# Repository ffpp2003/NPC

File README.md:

# NPC
Demostracion conceptual funcional de un neutralizador de puntos ciegos para autos

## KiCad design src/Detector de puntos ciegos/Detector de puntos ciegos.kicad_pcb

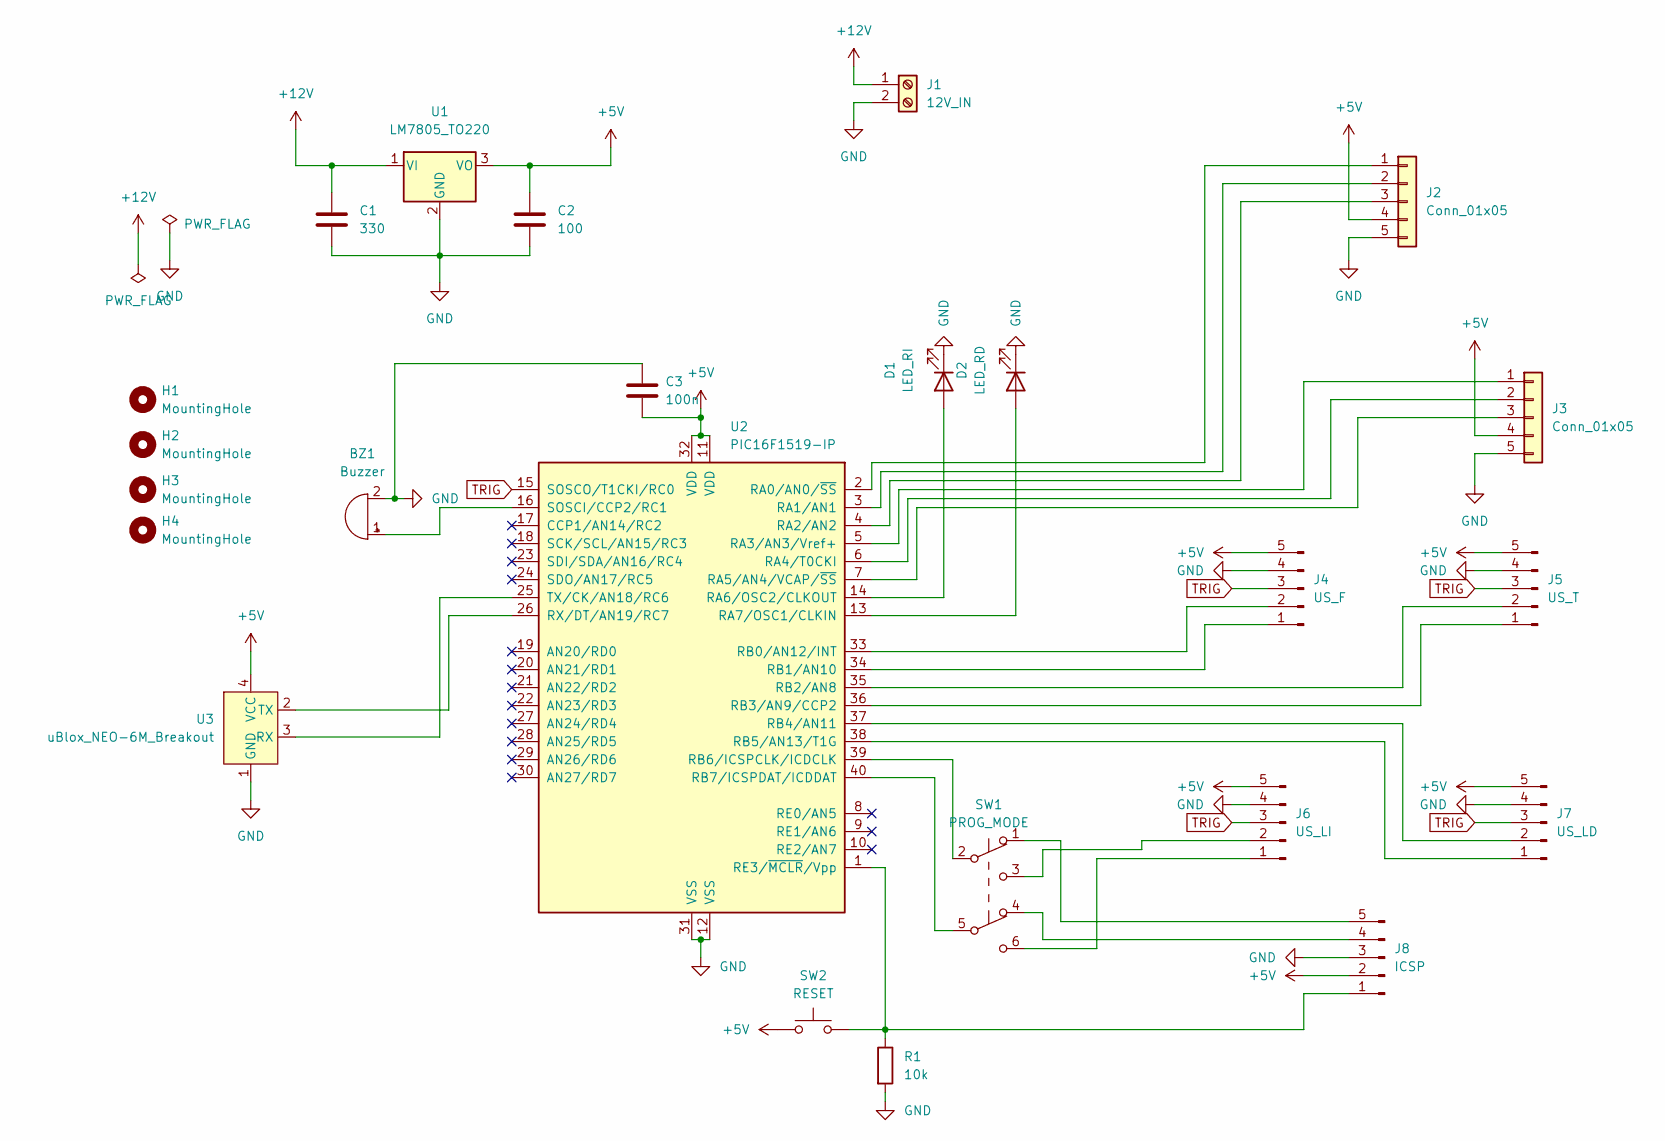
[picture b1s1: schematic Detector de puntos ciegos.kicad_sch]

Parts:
BZ1: Buzzer; Buzzer_12x9.5RM7.6
C1: 330; C_Disc_D5.0mm_W2.5mm_P5.00mm
C2: 100; C_Disc_D5.0mm_W2.5mm_P5.00mm
C3: 100n; C_Disc_D5.0mm_W2.5mm_P5.00mm
D1: LED_RI; PinHeader_1x02_P2.54mm_Vertical
D2: LED_RD; PinHeader_1x02_P2.54mm_Vertical
H1, H2, H3, H4: MountingHole; MountingHole_3.2mm_M3
J1: 12V_IN; TerminalBlock_Phoenix_MKDS-1,5-2-5.08_1x02_P5.08mm_Horizont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
J2, J3: Conn_01x05; PinHeader_1x05_P2.54mm_Vertical
J4: US_F; PinHeader_1x05_P2.54mm_Vertical
J5: US_T; PinHeader_1x05_P2.54mm_Vertical
J6: US_LI; PinHeader_1x05_P2.54mm_Vertical
J7: US_LD; PinHeader_1x05_P2.54mm_Vertical
J8: ICSP; PinHeader_1x06_P2.54mm_Vertical
R1: 10k; R_Axial_DIN0207_L6.3mm_D2.5mm_P2.54mm_Vertical
SW1: PROG_MODE; SW_Push_2P2T_Toggle_CK_PVA2OAH5xxxxxxV2
SW2: RESET; TE_FSM8JRT
U1: LM7805_TO220; TO-220-3_Vertical
U2: PIC16F1519-IP; DIP-40_W15.24mm_Socket_LongPads
U3: uBlox_NEO-6M_Breakout; uBlox-NEO-6M_Breakout

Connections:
+5V: C2.1, C3.1, J2.4, J3.4, J4.5, J5.5, J6.5, J7.5, J8.2, SW2.1, U1.3 (VO), U2.11 (VDD), U2.32 (VDD), U3.4 (VCC)
+12V: C1.1, J1.1, U1.1 (VI)
GND: BZ1.2 (+), C1.2, C2.2, C3.2, D1.1 (K), D2.1 (K), J1.2, J2.5, J3.5, J4.4, J5.4, J6.4, J7.4, J8.3, R1.2, U1.2 (GND), U2.12 (VSS), U2.31 (VSS), U3.1 (GND)
unnamed: BZ1.1 (-), U2.16 (SOSCI/CCP2/RC1)
unnamed: D1.2 (A), U2.14 (RA6/OSC2/CLKOUT)
unnamed: D2.2 (A), U2.13 (RA7/OSC1/CLKIN)
unnamed: J2.1, U2.2 (RA0/AN0/~SS)
unnamed: J2.2, U2.3 (RA1/AN1)
unnamed: J2.3, U2.4 (RA2/AN2)
unnamed: J3.1, U2.5 (RA3/AN3/Vref+)
unnamed: J3.2, U2.6 (RA4/T0CKI)
unnamed: J3.3, U2.7 (RA5/AN4/VCAP/~SS)
unnamed: J4.1, U2.34 (RB1/AN10)
unnamed: J4.2, U2.33 (RB0/AN12/INT)
unnamed: J5.1, U2.36 (RB3/AN9/CCP2)
unnamed: J5.2, U2.35 (RB2/AN8)
unnamed: J6.1, SW1.6 (C)
unnamed: J6.2, SW1.3 (C)
unnamed: J7.1, U2.38 (RB5/AN13/T1G)
unnamed: J7.2, U2.37 (RB4/AN11)
unnamed: J8.1, R1.1, SW2.2, U2.1 (RE3/~MCLR/Vpp)
unnamed: J8.4, SW1.4 (A)
unnamed: J8.5, SW1.1 (A)
unnamed: SW1.2 (B), U2.39 (RB6/ICSPCLK/ICDCLK)
unnamed: SW1.5 (B), U2.40 (RB7/ICSPDAT/ICDDAT)
unnamed: U2.25 (TX/CK/AN18/RC6), U3.3 (RX)
unnamed: U2.26 (RX/DT/AN19/RC7), U3.2 (TX)
TRIG: J4.3, J5.3, J6.3, J7.3, U2.15 (SOSCO/T1CKI/RC0)

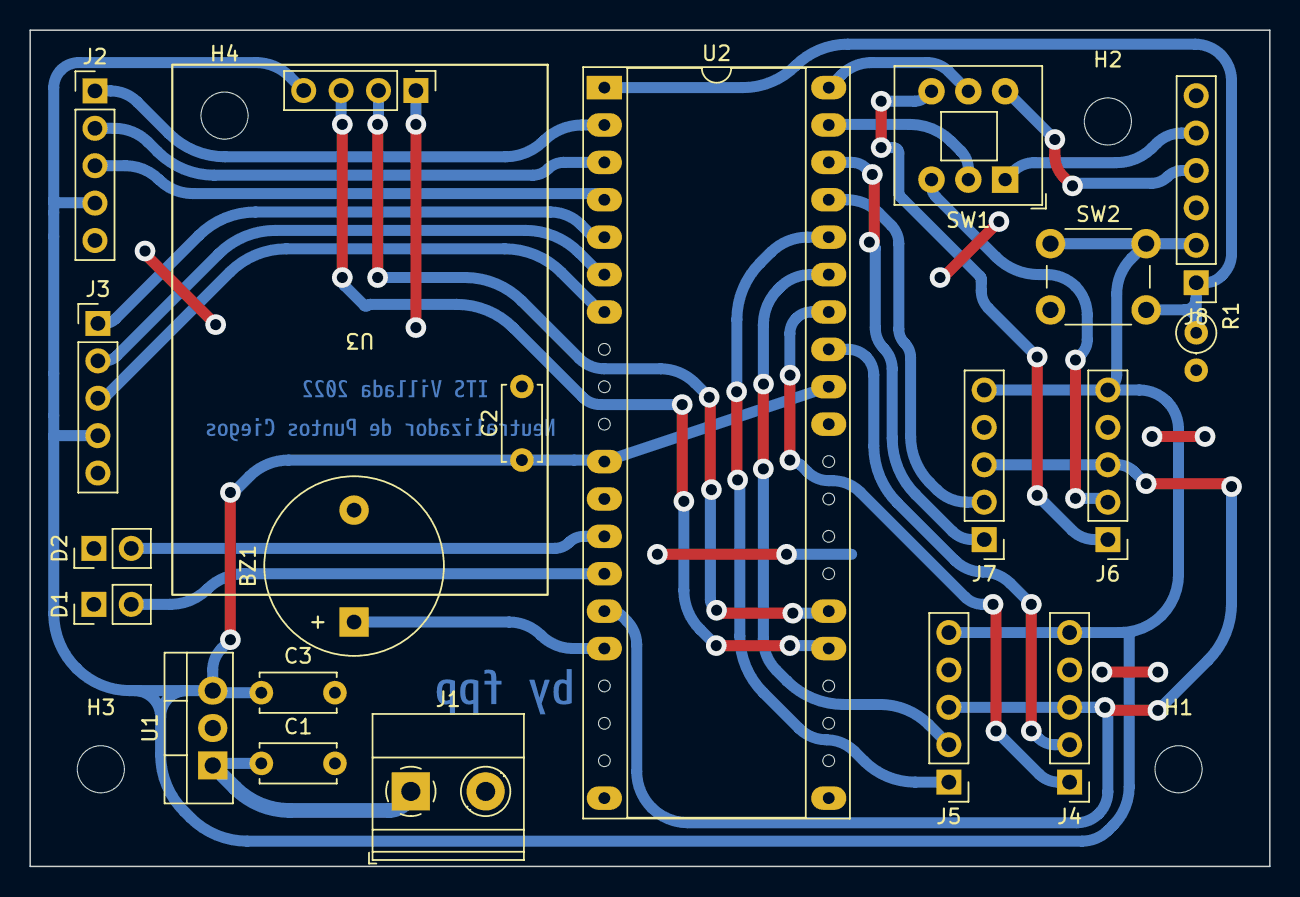
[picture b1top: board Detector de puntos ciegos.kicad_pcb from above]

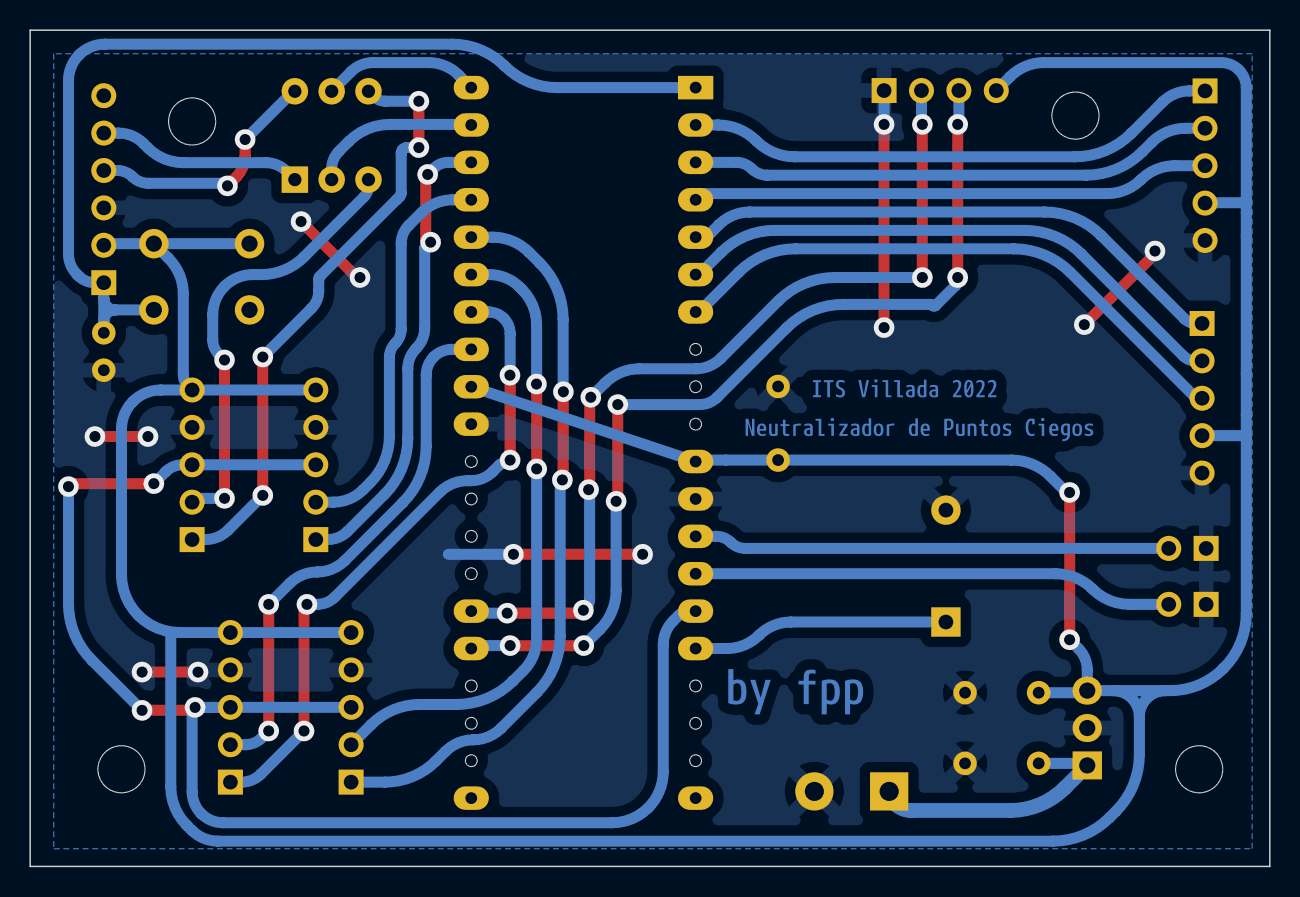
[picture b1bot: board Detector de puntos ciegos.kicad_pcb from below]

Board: 2 copper layers, 84.2 x 56.8 mm, 27 parts (3 on the bottom side), 28 nets.

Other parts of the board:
kibuzzard-636CFA59: G***; kibuzzard-636CFA59
kibuzzard-636CFA96: G***; kibuzzard-636CFA96
kibuzzard-636CFAAE: G***; kibuzzard-636CFAAE

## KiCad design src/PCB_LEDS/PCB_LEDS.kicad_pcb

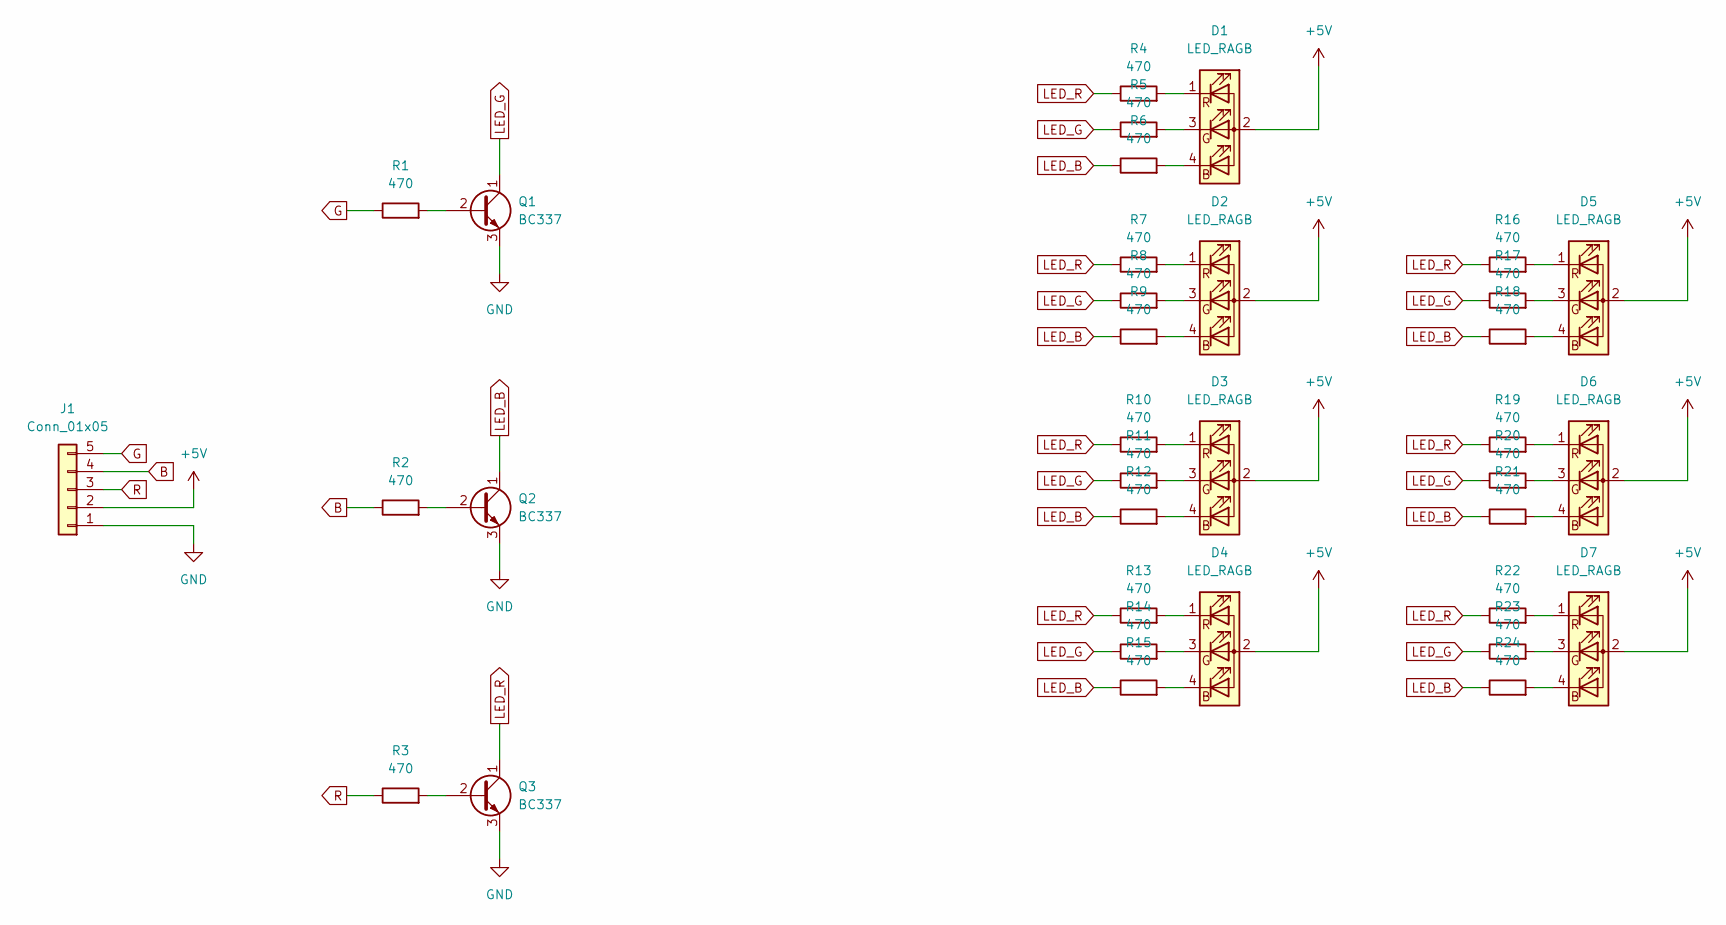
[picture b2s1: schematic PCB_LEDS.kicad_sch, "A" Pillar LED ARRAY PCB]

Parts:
D1, D2, D3, D4, D5, D6, D7: LED_RAGB; LED_D5.0mm-4_RGB_Wide_Pins
J1: Conn_01x05; PinHeader_1x05_P2.54mm_Vertical
Q1, Q2, Q3: BC337; TO-92_Inline_Wide
R1, R2, R3, R4, R5, R6, R7, R8, R9, R10, R11, R12, R13, R14, R15, R16, R17, R18, R19, R20, R21, R22, R23, R24: 470; R_0603_1608Metric_Pad0.98x0.95mm_HandSolder

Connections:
+5V: D1.2 (A), D2.2 (A), D3.2 (A), D4.2 (A), D5.2 (A), D6.2 (A), D7.2 (A), J1.2
B: J1.4, R2.1
G: J1.5, R1.1
GND: J1.1, Q1.3 (E), Q2.3 (E), Q3.3 (E)
LED_B: Q2.1 (C), R6.1, R9.1, R12.1, R15.1, R18.1, R21.1, R24.1
LED_G: Q1.1 (C), R5.1, R8.1, R11.1, R14.1, R17.1, R20.1, R23.1
LED_R: Q3.1 (C), R4.1, R7.1, R10.1, R13.1, R16.1, R19.1, R22.1
unnamed: D1.1 (RK), R4.2
unnamed: D1.3 (GK), R5.2
unnamed: D1.4 (BK), R6.2
unnamed: D2.1 (RK), R7.2
unnamed: D2.3 (GK), R8.2
unnamed: D2.4 (BK), R9.2
unnamed: D3.1 (RK), R10.2
unnamed: D3.3 (GK), R11.2
unnamed: D3.4 (BK), R12.2
unnamed: D4.1 (RK), R13.2
unnamed: D4.3 (GK), R14.2
unnamed: D4.4 (BK), R15.2
unnamed: D5.1 (RK), R16.2
unnamed: D5.3 (GK), R17.2
unnamed: D5.4 (BK), R18.2
unnamed: D6.1 (RK), R19.2
unnamed: D6.3 (GK), R20.2
unnamed: D6.4 (BK), R21.2
unnamed: D7.1 (RK), R22.2
unnamed: D7.3 (GK), R23.2
unnamed: D7.4 (BK), R24.2
unnamed: Q1.2 (B), R1.2
unnamed: Q2.2 (B), R2.2
unnamed: Q3.2 (B), R3.2
R: J1.3, R3.1

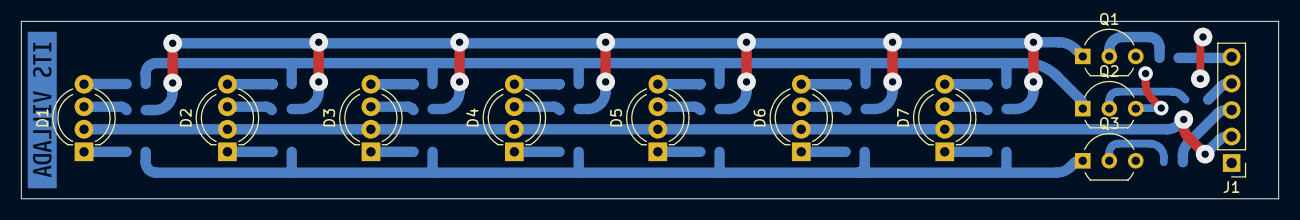
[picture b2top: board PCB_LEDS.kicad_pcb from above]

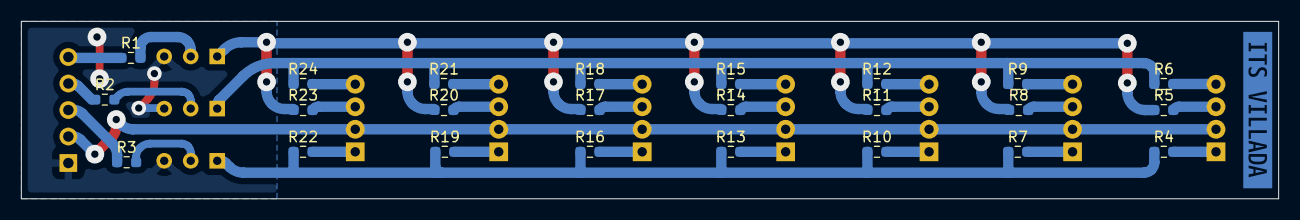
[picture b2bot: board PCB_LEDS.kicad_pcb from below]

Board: 2 copper layers, 120.5 x 17.0 mm, 36 parts (25 on the bottom side), 32 nets.

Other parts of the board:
kibuzzard-6352A8D4: G***; kibuzzard-6352A8D4

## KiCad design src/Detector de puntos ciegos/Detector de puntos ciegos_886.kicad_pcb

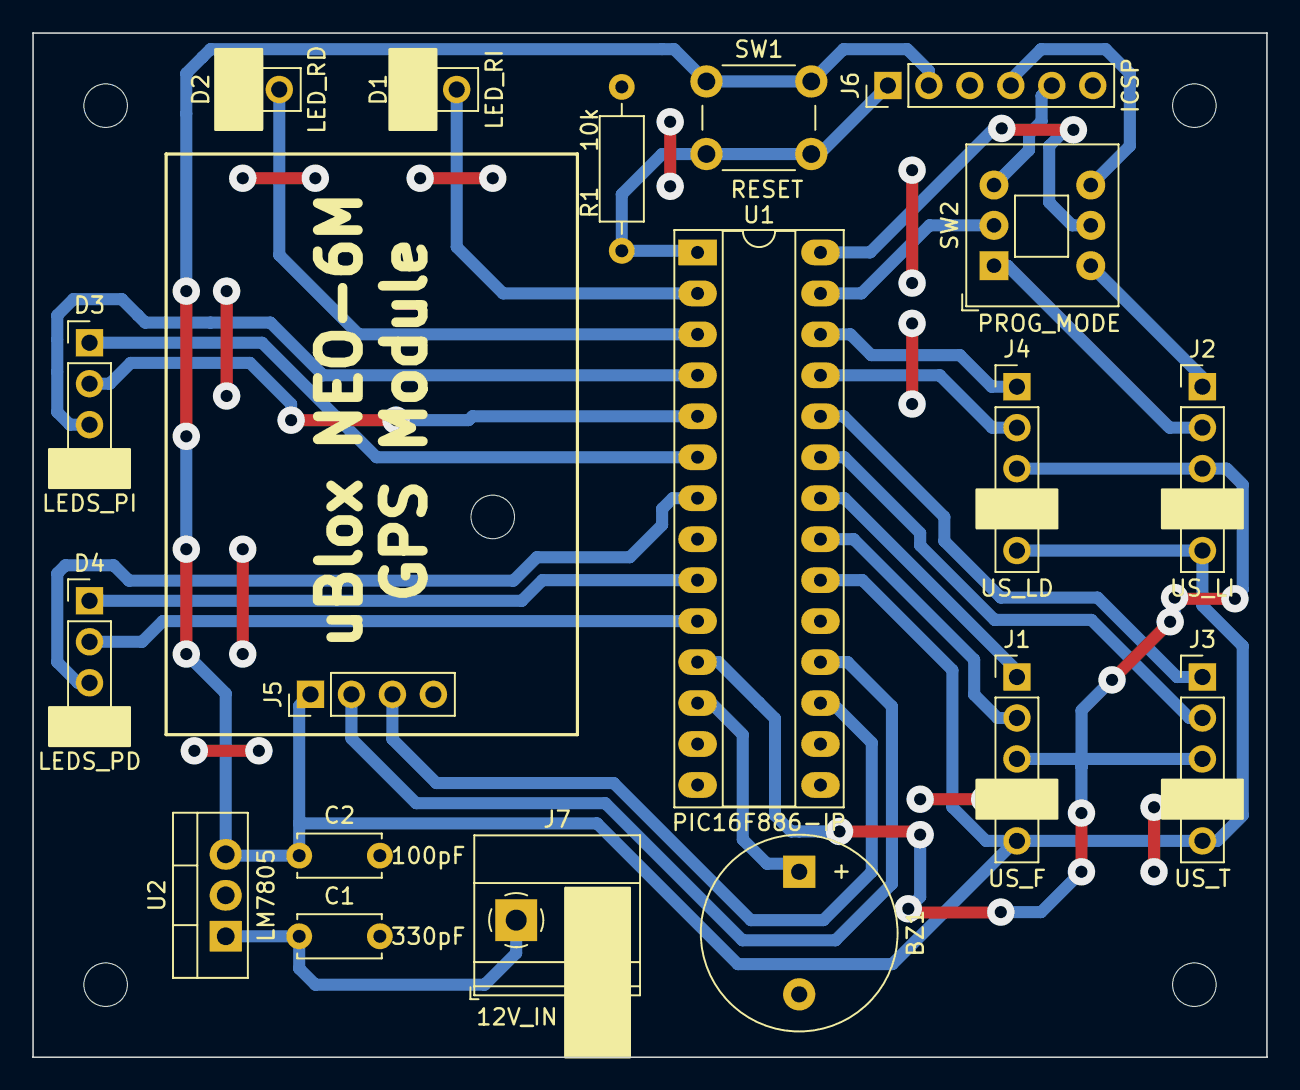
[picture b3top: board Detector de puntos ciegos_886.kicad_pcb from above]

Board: 2 copper layers, 76.5 x 63.5 mm, 19 parts (0 on the bottom side), 28 nets.

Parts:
BZ1: Buzzer; Buzzer_12x9.5RM7.6
C1: 330pF; C_Disc_D5.0mm_W2.5mm_P5.00mm
C2: 100pF; C_Disc_D5.0mm_W2.5mm_P5.00mm
D1: LED_RI; PinHeader_1x02_P2.54mm_Vertical
D2: LED_RD; PinHeader_1x02_P2.54mm_Vertical
D3: LEDS_PI; PinHeader_1x04_P2.54mm_Vertical
D4: LEDS_PD; PinHeader_1x04_P2.54mm_Vertical
J1: US_F; PinHeader_1x05_P2.54mm_Vertical
J2: US_LI; PinHeader_1x05_P2.54mm_Vertical
J3: US_T; PinHeader_1x05_P2.54mm_Vertical
J4: US_LD; PinHeader_1x05_P2.54mm_Vertical
J5: GPS; PinHeader_1x04_P2.54mm_Vertical
J6: ICSP; PinHeader_1x06_P2.54mm_Vertical
J7: 12V_IN; TerminalBlock_Phoenix_MKDS-1,5-2-5.08_1x02_P5.08mm_Horizont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
R1: 10k; R_Axial_DIN0207_L6.3mm_D2.5mm_P10.16mm_Horizontal
SW1: RESET; SW_PUSH_6mm_H5mm
SW2: PROG_MODE; SW_Push_2P2T_Toggle_CK_PVA2OAH5xxxxxxV2
U1: PIC16F886-IP; DIP-28_W7.62mm_Socket_LongPads
U2: LM7805; TO-220-3_Vertical

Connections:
+5V: C2.1, J1.5, J2.5, J3.5, J4.5, J5.1, J6.2, SW1.1, U1.20 (VDD), U2.3 (VO)
+12V: C1.1, J7.1, U2.1 (VI)
GND: BZ1.2 (+), C1.2, C2.2, D1.1 (K), D2.1 (K), D3.4 (K), D4.4 (K), J1.4, J2.4, J3.4, J4.4, J5.4, J6.3, J7.2, R1.2, U1.8 (VSS), U1.19 (VSS), U2.2 (GND)
unnamed: BZ1.1 (-), U1.12 (RC1/T1OSI/CCP2)
unnamed: D1.2 (A), U1.2 (ULPWU/C12IN0-/AN0/RA0)
unnamed: D2.2 (A), U1.3 (C12IN1-/AN1/RA1)
unnamed: D3.1 (RA), U1.6 (T0CKI/C1OUT/RA4)
unnamed: D3.2 (GA), U1.5 (C1IN+/Vref+/AN3/RA3)
unnamed: D3.3 (BA), U1.4 (CVref/C2IN1+/Vref-/AN2/RA2)
unnamed: D4.1 (RA), U1.9 (CLKIN/OSC1/RA7)
unnamed: D4.2 (GA), U1.10 (CLKOUT/OSC2/RA6)
unnamed: D4.3 (BA), U1.7 (~SS/C2OUT/AN4/RA5)
unnamed: J1.1, U1.22 (P1C/AN10/RB1)
unnamed: J1.2, U1.21 (INT/AN12/RB0)
unnamed: J2.1, SW2.4 (A)
unnamed: J2.2, SW2.1 (A)
unnamed: J3.1, U1.24 (PGM/C12IN2-/AN8/RB3)
unnamed: J3.2, U1.23 (P1B/AN8/RB2)
unnamed: J4.1, U1.26 (~T1G/AN13/RB5)
unnamed: J4.2, U1.25 (P1D/AN11/RB4)
unnamed: J6.1, R1.1, SW1.2, U1.1 (RE3/~MCLR/Vpp)
unnamed: J6.4, SW2.6 (C)
unnamed: J6.5, SW2.3 (C)
unnamed: SW2.2 (B), U1.27 (ICSPCLK/RB6)
unnamed: SW2.5 (B), U1.28 (ICSPDAT/RB7)
RX: J5.2, U1.18 (RC7/RX/DT)
TRIG: J1.3, J2.3, J3.3, J4.3, U1.11 (RC0/T1OSO/T1CK1)
TX: J5.3, U1.17 (RC6/TX/CK)

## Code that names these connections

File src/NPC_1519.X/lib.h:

#ifndef LIB_H
#define LIB_H

#include <xc.h>

#define UART_TRIS_RX     TRISCbits.TRISC7
#define UART_TRIS_TX     TRISCbits.TRISC6
#define OVRPSS_V_RNGE 175 // distance from car to end of mirror view at rear bumper alignment

#define TRIG PORTCbits.RC0
//#define BUZZ PORTAbits.RA6
#define BUZZ PORTCbits.RC1
#define SLOWUSA 0
#define SLOWUSB 1
#define GP_LED  PORTAbits.RA0
#define BP_LED  PORTAbits.RA1
#define RP_LED  PORTAbits.RA2
#define GD_LED  PORTAbits.RA3
#define BD_LED  PORTAbits.RA4
#define RD_LED  PORTAbits.RA5
#define OVRPS_D PORTAbits.RA6
#define OVRPS_P PORTAbits.RA7

char *strtok_single(char *, char const *);
char UARTreadString(char *, unsigned char);
void UARTinit(const long, const unsigned char);
void UARTsendString(const char *, const unsigned char);
unsigned char us_to_cm(unsigned int);
unsigned char prom_us(unsigned int, unsigned int);
char updateSpeed(unsigned char *, float *, char *);
long map(long, long, long, long, long);
void beginSecuence();
void debugSS(float *, unsigned long *, unsigned char *);

#endif

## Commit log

2022-11-23 Create blank
2022-11-23 Main Code
2022-11-23 Main PCB
2022-11-23 LED PCB
2022-11-23 Renders
2022-11-23 Files created with Fusion 360 personal licence
2022-11-23 Schematics
2022-11-23 Made with google forms
